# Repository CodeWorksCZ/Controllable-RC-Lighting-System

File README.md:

# RC Lighting System - controlled by TX
A complete solution of LED lighting system for small plane. Controlled by Transmitter utilizing one PWM channel. Based on the PWM value you can either switch **Strobe light** or **Taxi / Landing lights**  on

## LEDS and their functions
| LED | Function | Position|Controlled by TX|
| --- | --- | --- |--- |
| GREEN | Position Light (On) | Right wing| NO |
| RED | Position Light (On) | Left wing | NO |
| WHITE | Strobe Light | Top of fuselage | YES |
| WHITE | Strobe Light | Bottom of fuselage | YES |
| WHITE - 2x | Strobe Light | Taxi / Landing Lights | YES |

## RC Transmitter setup
- tested on FrSky Taranis X9D+
- map you channel on 3 way switch

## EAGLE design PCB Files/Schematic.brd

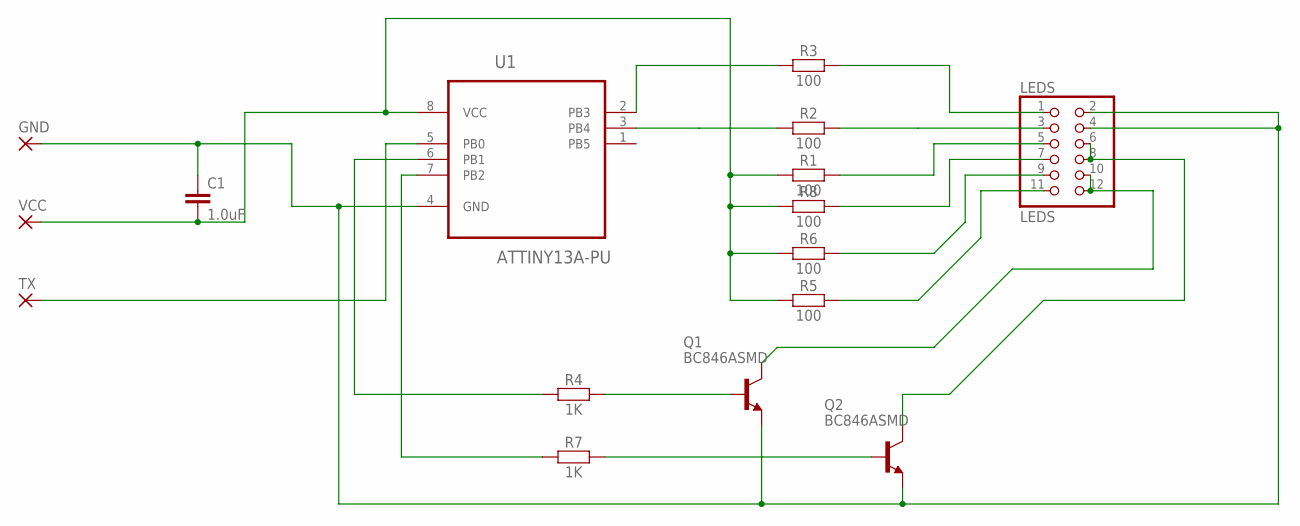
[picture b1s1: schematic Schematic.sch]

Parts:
C1: 1.0uF; 0805
GND: 3,17/1,1
LEDS: LEDS; 2X06/90
Q1, Q2: BC846ASMD; SOT23
R1, R2, R3, R5, R6, R8: 100; 0805
R4, R7: 1K; 0805
TX: 3,17/1,1
U1: ATTINY13A-PU; DIP254P762X533-8
VCC: 3,17/1,1

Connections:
unnamed: C1.1, GND.1, LEDS.2, LEDS.4, Q1.2 (E), Q2.2 (E), U1.4 (GND)
unnamed: C1.2, R1.1, R5.1, R6.1, R8.1, U1.8 (VCC), VCC.1
unnamed: TX.1, U1.5 (PB0)
unnamed: R3.1, U1.2 (PB3)
unnamed: LEDS.1, R3.2
unnamed: R2.1, U1.3 (PB4)
unnamed: LEDS.3, R2.2
unnamed: R7.1, U1.7 (PB2)
unnamed: LEDS.5, R1.2
unnamed: Q1.1 (B), R4.2
unnamed: R4.1, U1.6 (PB1)
unnamed: LEDS.9, R6.2
unnamed: LEDS.11, R5.2
unnamed: LEDS.10, LEDS.12, Q1.3 (C)
unnamed: Q2.1 (B), R7.2
unnamed: LEDS.7, R8.2
unnamed: LEDS.6, LEDS.8, Q2.3 (C)

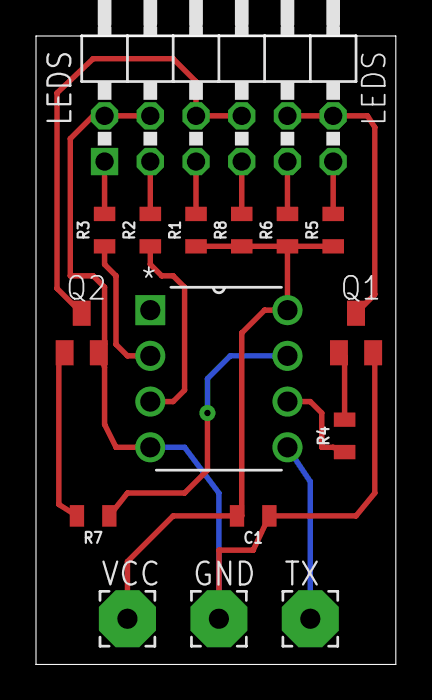
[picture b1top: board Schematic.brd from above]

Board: 2 copper layers, 20.0 x 34.9 mm, 16 parts (0 on the bottom side), 17 nets.

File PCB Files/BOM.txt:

Part Value        Device                    Package          Description                                                      
C1   1.0uF        1.0UF-0805-25V-(+80/-20%) 0805             1µF ceramic capacitors                                           
GND               3,17/1,1                  3,17/1,1         THROUGH-HOLE PAD                                                 
LEDS LEDS         PINHD-2X06_2.54-90°       2X06/90          PIN HEADER                                                       
Q1   BC846ASMD    BC846ASMD                 SOT23            NPN Transistor                                                   
Q2   BC846ASMD    BC846ASMD                 SOT23            NPN Transistor                                                   
R1   100          RESISTOR0805              0805             Generic Resistor Package                                         
R2   100          RESISTOR0805              0805             Generic Resistor Package                                         
R3   100          RESISTOR0805              0805             Generic Resistor Package                                         
R4   1K           RESISTOR0805              0805             Generic Resistor Package                                         
R5   100          RESISTOR0805              0805             Generic Resistor Package                                         
R6   100          RESISTOR0805              0805             Generic Resistor Package                                         
R7   1K           RESISTOR0805              0805             Generic Resistor Package                                         
R8   100          RESISTOR0805              0805             Generic Resistor Package                                         
TX                3,17/1,1                  3,17/1,1         THROUGH-HOLE PAD                                                 
U1   ATTINY13A-PU ATTINY13A-PU              DIP254P762X533-8 8-bit Microcontroller with 1K Bytes In-System Programmable Flash 
VCC               3,17/1,1                  3,17/1,1         THROUGH-HOLE PAD

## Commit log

2019-02-10 Update README.md
    Added Image
2019-02-10 Updated image
2019-02-10 Added Gerber file and Eagle schematics and board
2019-05-14 Edited BOM
2019-05-14 Removed .vscode directory
2019-05-14 Included Arduino.h
